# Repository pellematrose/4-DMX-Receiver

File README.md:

# DMX Receiver for the Raspberry Pi Pico

Firmware for a Raspberry Pi Pico (RP2040) that reads a DMX512 signal and drives four channels as RGBW — simultaneously as PWM on four power outputs and mirrored to a WS2812 pixel. It is operated with three buttons and a 128×64 OLED. Without a DMX signal, built-in auto effects run instead.
## Features
- DMX512 reception of the full 512-channel universe
- 4 output channels (R, G, B, W) from a freely selectable start address
- 800mA output current
- USB-C PD input 20V
- Configurable number of channels in use (1–4)
- RGBW output as PWM (500 Hz) and in parallel on a WS2812/NeoPixel
- OLED menu with buttons: start address, channel count, auto effect
- Settings are stored in EEPROM and restored on boot
- DMX takes priority: as soon as a signal is present, the auto effect is overridden
- Display turns off after 5 s of inactivity; the first button press wakes it
- At boot the firmware checks for DMX; without a signal the color fade starts automatically
## Auto effects

| Effect     | Description                                    |
| ---------- | ---------------------------------------------- |
| LED Auto   | Endless fade Red → Green → Blue                |
| Only White | White on all channels (W = 255 only)           |
| Blue-Green | Fade Blue ↔ Green with a 5 s pause at each end |
## Hardware / pinout

| Function    | GPIO | Note                                     |
| ----------- | ---- | ---------------------------------------- |
| DMX RX      | 0    | `dmxInput.begin(0, 1, 512)` – RX = GPIO0 |
| Button UP   | 3    | to GND, internal pull-up                 |
| Button MODE | 4    | to GND, internal pull-up                 |
| Button DOWN | 5    | to GND, internal pull-up                 |
| LED White   | 9    | PWM                                      |
| LED Blue    | 10   | PWM                                      |
| LED Green   | 11   | PWM                                      |
| LED Red     | 12   | PWM                                      |
| OLED SDA    | 14   | I2C (Wire1)                              |
| OLED SCL    | 15   | I2C (Wire1)                              |
| WS2812 data | 16   | 1 pixel                                  |
OLED: SSD1306, 128×64, I2C address `0x3C`.

The DMX input needs an RS-485 transceiver (e.g. MAX485) running at 3.3 V; twist the A/B pair and don't forget bus termination at both ends.
## Operation
**Main menu** (MODE to enter, UP/DOWN to scroll):
1. `DMX` → set start address and channel count
2. `AUTO` → choose an auto effect and start it with MODE

**In the DMX submenu:** MODE switches between *Start Addr* and *Num Channel*. UP/DOWN changes the value; MODE on the second field saves and returns. The address is automatically clamped so all channels fit inside the universe (max. `512 - channels + 1`).

**In the AUTO submenu:** UP/DOWN selects an effect, MODE starts it and returns to the main menu.
## Build
Platformio with the **Raspberry Pi Pico / RP2040** core (Earle Philhower).
Required libraries:
- `DmxInput` (DMX input via PIO, by )
- `Adafruit SSD1306`
- `Adafruit GFX Library`
- `Adafruit NeoPixel`
- `EEPROM` (included in the RP2040 core)
Board: *Raspberry Pi Pico*, sketch: `dmx_receiver.ino`.
## Notes
- When idle without DMX, the display does not refresh continuously — it redraws only on button presses and every 250 ms in the main menu.
- DMX handling is non-blocking, so buttons and display stay responsive even when the signal drops out.
- `buffer[0]` is the DMX start byte, which is why channel evaluation begins at `address + i` in the buffered universe.
# Not included in the Repo
- Some LEDs to light up
## License
GPL-3.0-or-later, for Firmware, see `LICENSE`. Copyright (c) 2026 Per-Simon Saal.

CERN-OHL-S-2.0, for Hardware and Enclosure, see `LICENSE`. Copyriht (c) 2026 Per-Simon Saal.

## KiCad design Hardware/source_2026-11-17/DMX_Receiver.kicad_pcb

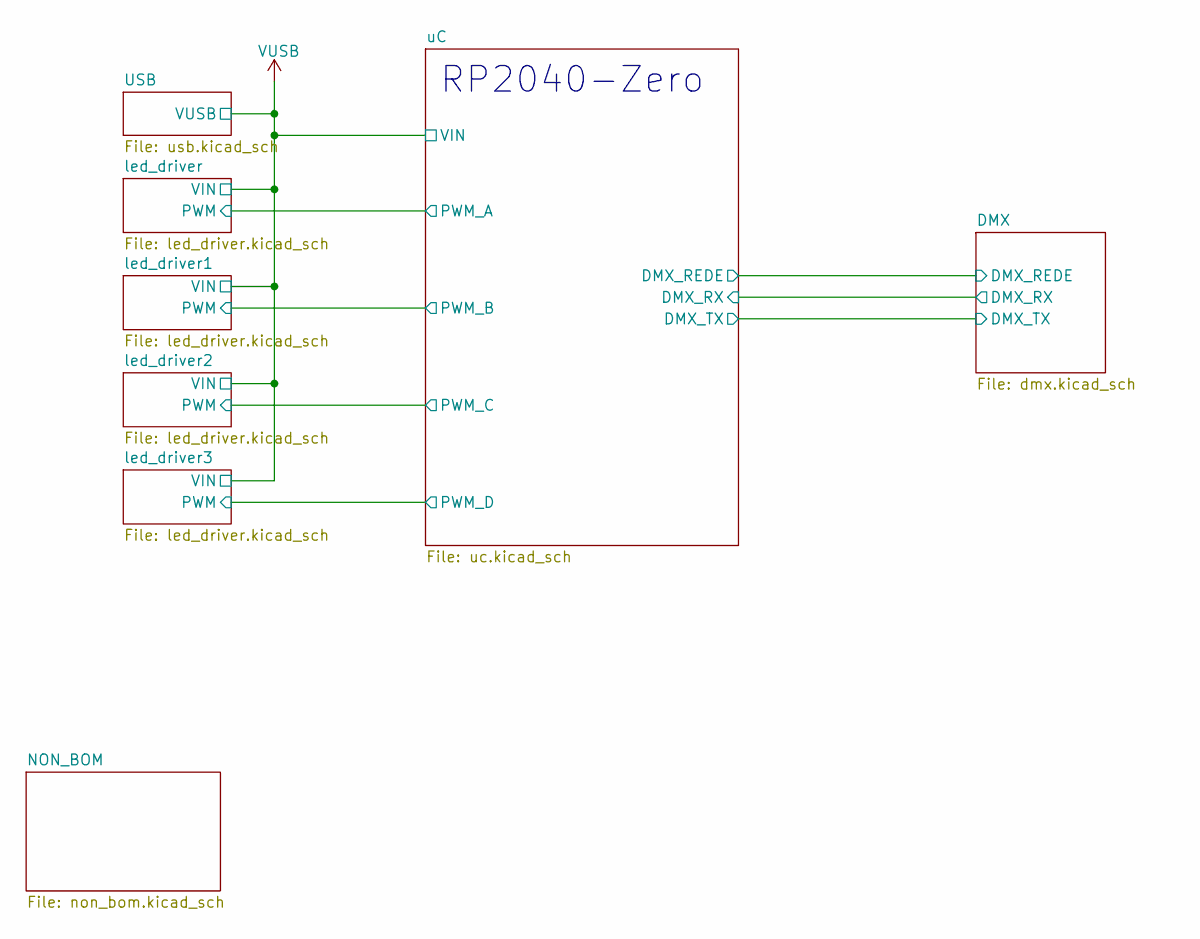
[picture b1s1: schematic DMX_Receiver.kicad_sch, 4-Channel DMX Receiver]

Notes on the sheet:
RP2040-Zero

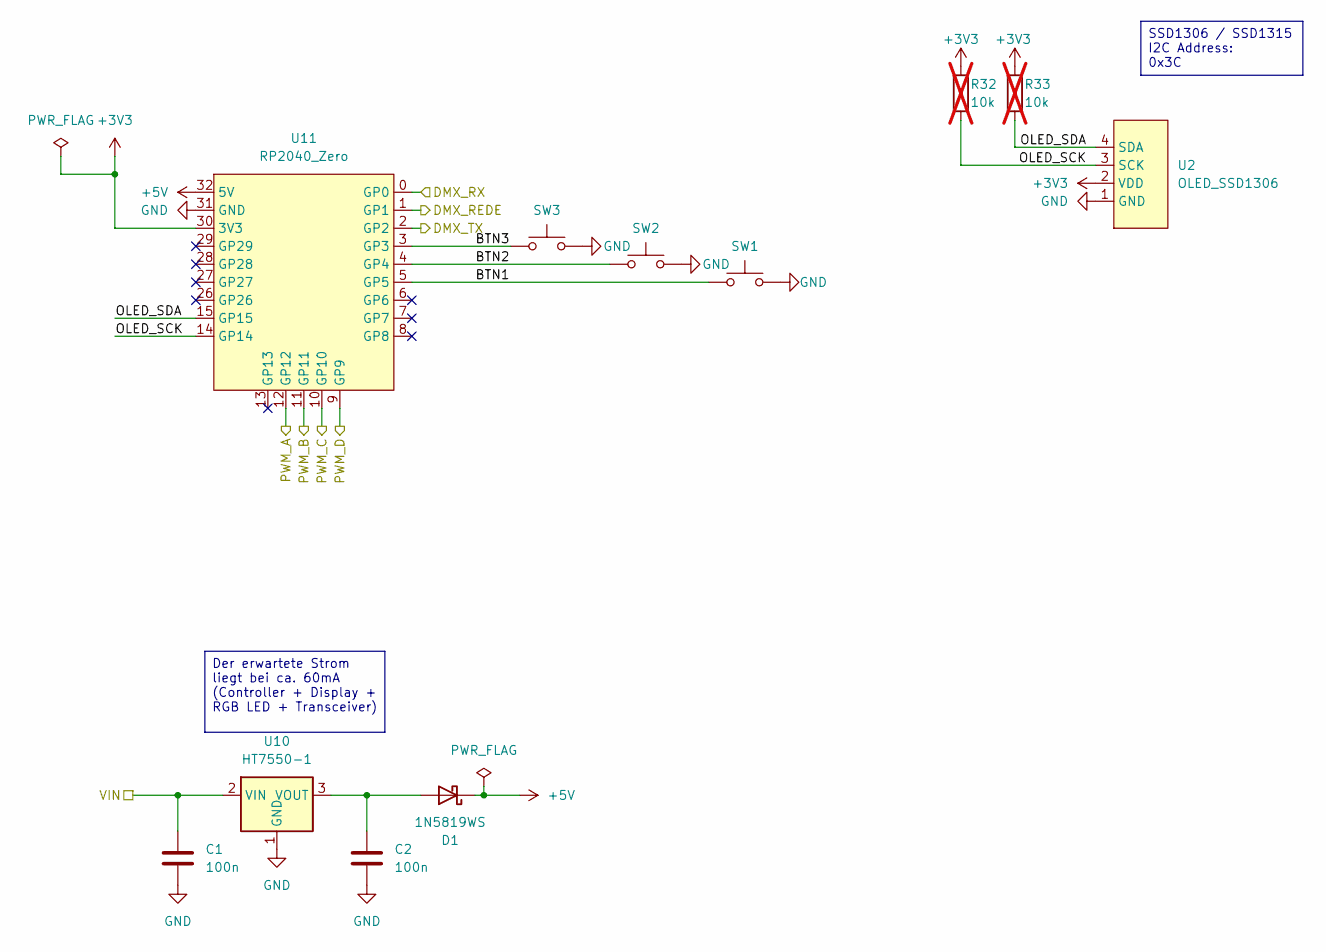
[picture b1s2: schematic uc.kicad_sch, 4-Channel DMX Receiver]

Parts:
C1, C2: 100n; C_0603_1608Metric; LCSC C14663
D1: 1N5819WS; D_SOD-323; LCSC C191023
R32, R33: 10k; R_0603_1608Metric; LCSC C25804; not fitted
SW1, SW2, SW3: SW_MEC_5G; Xunpu TS-1088
U2: OLED_SSD1306; SSD1306_0.96_Oled_wo_Holes
U10: HT7550-1; SOT-89-3; LCSC C16106
U11: RP2040_Zero; RP2040-Zero_SMD

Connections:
+3V3: R32.1, R33.1, U2.2 (VDD), U11.30 (3V3); also elsewhere on the board
+5V: D1.1 (K), U11.32 (5V)
/DMX/DMX_REDE: U11.1 (GP1); also elsewhere on the board
/DMX/DMX_RX: U11.0 (GP0); also elsewhere on the board
/DMX/DMX_TX: U11.2 (GP2); also elsewhere on the board
/led_driver1/PWM: U11.11 (GP11); also elsewhere on the board
/led_driver2/PWM: U11.10 (GP10); also elsewhere on the board
/led_driver3/PWM: U11.9 (GP9); also elsewhere on the board
/led_driver/PWM: U11.12 (GP12); also elsewhere on the board
/uC/BTN1: SW1.2 (B), U11.5 (GP5)
/uC/BTN2: SW2.2 (B), U11.4 (GP4)
/uC/BTN3: SW3.2 (B), U11.3 (GP3)
/uC/OLED_SCK: R32.2, U2.3 (SCK), U11.14 (GP14)
/uC/OLED_SDA: R33.2, U2.4 (SDA), U11.15 (GP15)
GND: C1.2, C2.2, SW1.1 (A), SW2.1 (A), SW3.1 (A), U2.1 (GND), U10.1 (GND), U11.31 (GND); also elsewhere on the board
unnamed: C2.1, D1.2 (A), U10.3 (VOUT)
VUSB: C1.1, U10.2 (VIN); also elsewhere on the board

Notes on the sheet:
Der erwartete Strom liegt bei ca. 60mA (Controller + Display + RGB LED + Transceiver)
SSD1306 / SSD1315 I2C Address: 0x3C

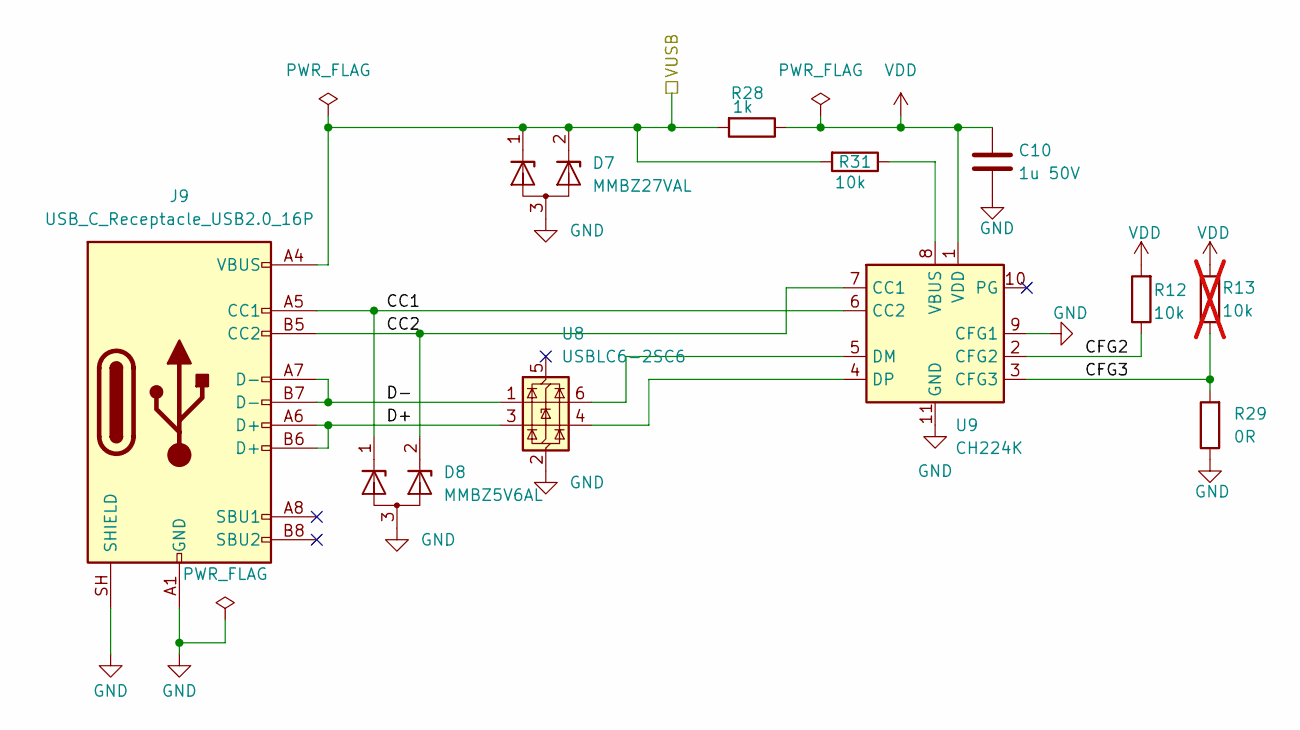
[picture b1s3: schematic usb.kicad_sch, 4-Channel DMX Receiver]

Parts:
C10: 1u 50V; C_0603_1608Metric; LCSC C15849
D7: MMBZ27VAL; SOT-23; LCSC C502597
D8: MMBZ5V6AL; SOT-23; LCSC C502591
J9: USB_C_Receptacle_USB2.0_16P; USB_C_Receptacle_GCT_USB4105-xx-A_16P_TopMnt_Horizontal; LCSC C2988369
R12, R31: 10k; R_0603_1608Metric; LCSC C25804
R13: 10k; R_0603_1608Metric; LCSC C25804; not fitted
R28: 1k; R_0603_1608Metric; LCSC C21190
R29: 0R; R_0603_1608Metric; LCSC C25804
U8: USBLC6-2SC6; SOT-23-6; LCSC C7519
U9: CH224K; SSOP-10-1EP_3.9x4.9mm_P1mm_EP2.1x3.3mm; LCSC C970725

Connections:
/USB/CC1: D8.1 (K), J9.A5 (CC1), U9.6 (CC2)
/USB/CC2: D8.2 (K), J9.B5 (CC2), U9.7 (CC1)
/USB/CFG2: R12.1, U9.2 (CFG2)
/USB/CFG3: R13.1, R29.2, U9.3 (CFG3)
/USB/D+: J9.A6 (D+), J9.B6 (D+), U8.3 (I/O2)
/USB/D-: J9.A7 (D-), J9.B7 (D-), U8.1 (I/O1)
GND: C10.1, D7.3 (A), D8.3 (A), J9.A1 (GND), J9.A12 (GND), J9.B1 (GND), J9.B12 (GND), J9.SH (SHIELD), R29.1, U8.2 (GND), U9.9 (CFG1), U9.11 (GND); also elsewhere on the board
unnamed: U8.6 (I/O1), U9.5 (DM)
unnamed: U8.4 (I/O2), U9.4 (DP)
unnamed: R31.1, U9.8 (VBUS)
VDD: C10.2, R12.2, R13.2, R28.1, U9.1 (VDD)
VUSB: D7.1 (K), D7.2 (K), J9.A4 (VBUS), J9.A9 (VBUS), J9.B4 (VBUS), J9.B9 (VBUS), R28.2, R31.2; also elsewhere on the board

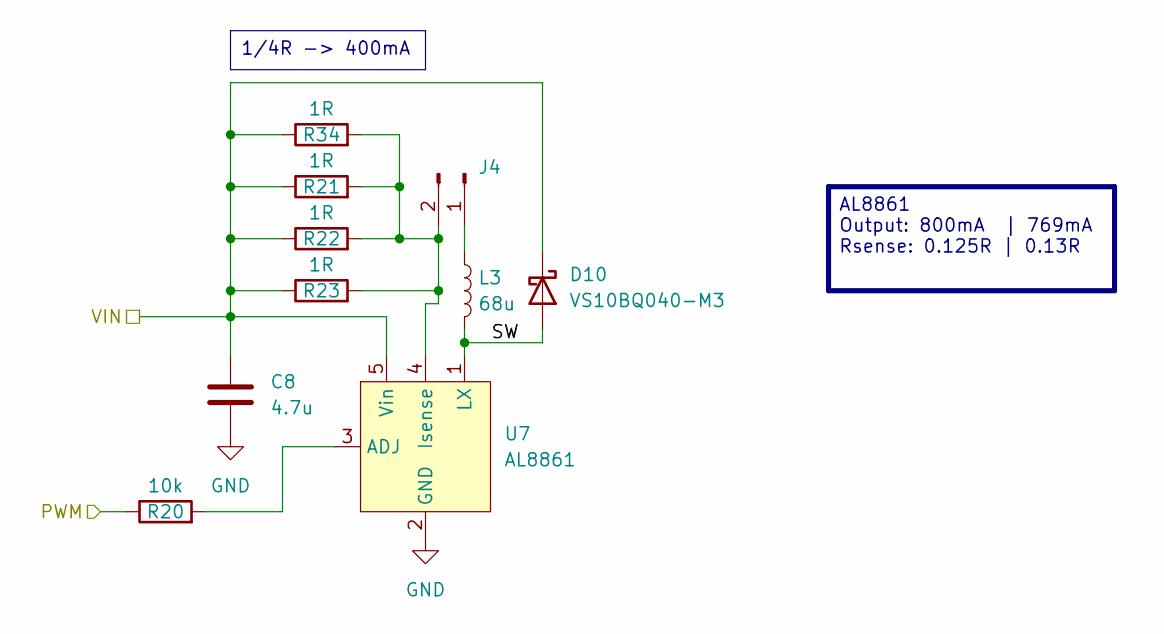
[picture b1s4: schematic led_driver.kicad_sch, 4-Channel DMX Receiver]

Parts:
C8: 4.7u; C_1206_3216Metric; LCSC C29823
D10: VS10BQ040-M3; D_SMB; LCSC C28646277
J4: Conn_01x02_Pin; PinHeader_1x02_P2.54mm_Vertical
L3: 68u; L_TDK_VLS6045EX_VLS6045AF; LCSC C404506
R20: 10k; R_0603_1608Metric; LCSC C25804
R21, R22, R23, R34: 1R; R_0603_1608Metric; LCSC C22936
U7: AL8861; SOT-23-5; LCSC C581338

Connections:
/led_driver/PWM: R20.1; also elsewhere on the board
/led_driver/SW: D10.2 (A), L3.2, U7.1 (LX)
GND: C8.2, U7.2 (GND); also elsewhere on the board
unnamed: J4.1, L3.1
unnamed: J4.2, R21.2, R22.2, R23.2, R34.2, U7.4 (Isense)
unnamed: R20.2, U7.3 (ADJ)
VUSB: C8.1, D10.1 (K), R21.1, R22.1, R23.1, R34.1, U7.5 (Vin); also elsewhere on the board

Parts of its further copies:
C3, C7, C9: 4.7u; C_1206_3216Metric; LCSC C29823
D3, D4, D5: VS10BQ040-M3; D_SMB; LCSC C28646277
J5, J7, J8: Conn_01x02_Pin; PinHeader_1x02_P2.54mm_Vertical
L1, L2, L4: 68u; L_TDK_VLS6045EX_VLS6045AF; LCSC C404506
R2, R3, R4, R5, R15, R16, R17, R18, R24, R25, R26, R27: 1R; R_0603_1608Metric; LCSC C22936
R14, R19, R35: 10k; R_0603_1608Metric; LCSC C25804
U4, U5, U6: AL8861; SOT-23-5; LCSC C581338

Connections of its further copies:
/led_driver1/PWM: R14.1; also elsewhere on the board
/led_driver1/SW: D3.2 (A), L1.2, U4.1 (LX)
/led_driver2/PWM: R19.1; also elsewhere on the board
/led_driver2/SW: D4.2 (A), L2.2, U5.1 (LX)
/led_driver3/PWM: R35.1; also elsewhere on the board
/led_driver3/SW: D5.2 (A), L4.2, U6.1 (LX)
GND: C3.2, C7.2, C9.2, U4.2 (GND), U5.2 (GND), U6.2 (GND); also elsewhere on the board
unnamed: J5.1, L1.1
unnamed: J5.2, R2.2, R3.2, R4.2, R5.2, U4.4 (Isense)
unnamed: J7.1, L2.1
unnamed: J7.2, R15.2, R16.2, R17.2, R18.2, U5.4 (Isense)
unnamed: J8.1, L4.1
unnamed: J8.2, R24.2, R25.2, R26.2, R27.2, U6.4 (Isense)
unnamed: R14.2, U4.3 (ADJ)
unnamed: R19.2, U5.3 (ADJ)
unnamed: R35.2, U6.3 (ADJ)
VUSB: C3.1, C7.1, C9.1, D3.1 (K), D4.1 (K), D5.1 (K), R2.1, R3.1, R4.1, R5.1, R15.1, R16.1, R17.1, R18.1, R24.1, R25.1, R26.1, R27.1, U4.5 (Vin), U5.5 (Vin), U6.5 (Vin); also elsewhere on the board

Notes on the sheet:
AL8861 Output: 800mA | 769mA Rsense: 0.125R | 0.13R
1/4R -> 400mA

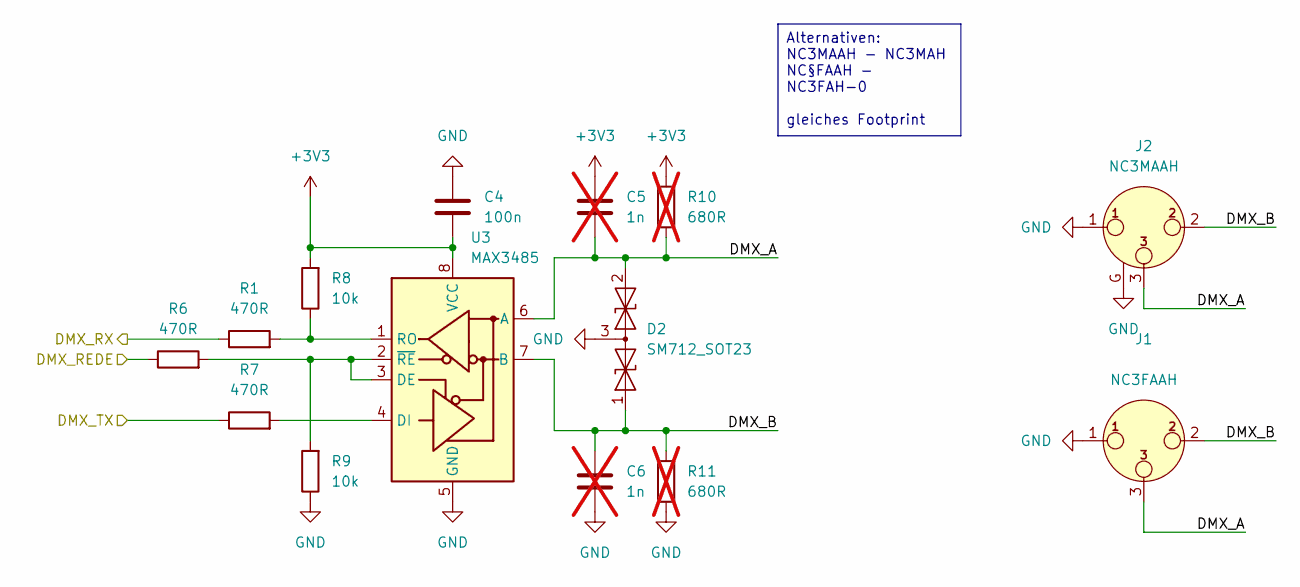
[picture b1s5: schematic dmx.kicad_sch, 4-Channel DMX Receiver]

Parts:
C4: 100n; C_0603_1608Metric; LCSC C14663
C5, C6: 1n; C_0603_1608Metric; not fitted
D2: SM712_SOT23; SOT-23; LCSC C521963
J1: NC3FAAH; Jack_XLR_Neutrik_NC3FAAH_Horizontal; LCSC C368463
J2: NC3MAAH; Jack_XLR_Neutrik_NC3MAAH_Horizontal; LCSC C368521
R1, R6, R7: 470R; R_0603_1608Metric; LCSC C23179
R8, R9: 10k; R_0603_1608Metric; LCSC C25804
R10, R11: 680R; R_0603_1608Metric; not fitted
U3: MAX3485; SOIC-8_3.9x4.9mm_P1.27mm; LCSC C8963

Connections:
+3V3: C4.2, C5.1, R8.2, R10.2, U3.8 (VCC); also elsewhere on the board
/DMX/DMX_A: C5.2, D2.2 (A2), J1.3, J2.3, R10.1, U3.6 (A)
/DMX/DMX_B: C6.1, D2.1 (A1), J1.2, J2.2, R11.2, U3.7 (B)
/DMX/DMX_REDE: R6.1; also elsewhere on the board
/DMX/DMX_RX: R1.1; also elsewhere on the board
/DMX/DMX_TX: R7.1; also elsewhere on the board
GND: C4.1, C6.2, D2.3 (common), J1.1, J2.1, J2.G, R9.1, R11.1, U3.5 (GND); also elsewhere on the board
unnamed: R6.2, R9.2, U3.2 (~RE), U3.3 (DE)
unnamed: R7.2, U3.4 (DI)
unnamed: R1.2, R8.1, U3.1 (RO)

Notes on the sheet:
Alternativen: NC3MAAH - NC3MAH NC§FAAH - NC3FAH-0 gleiches Footprint

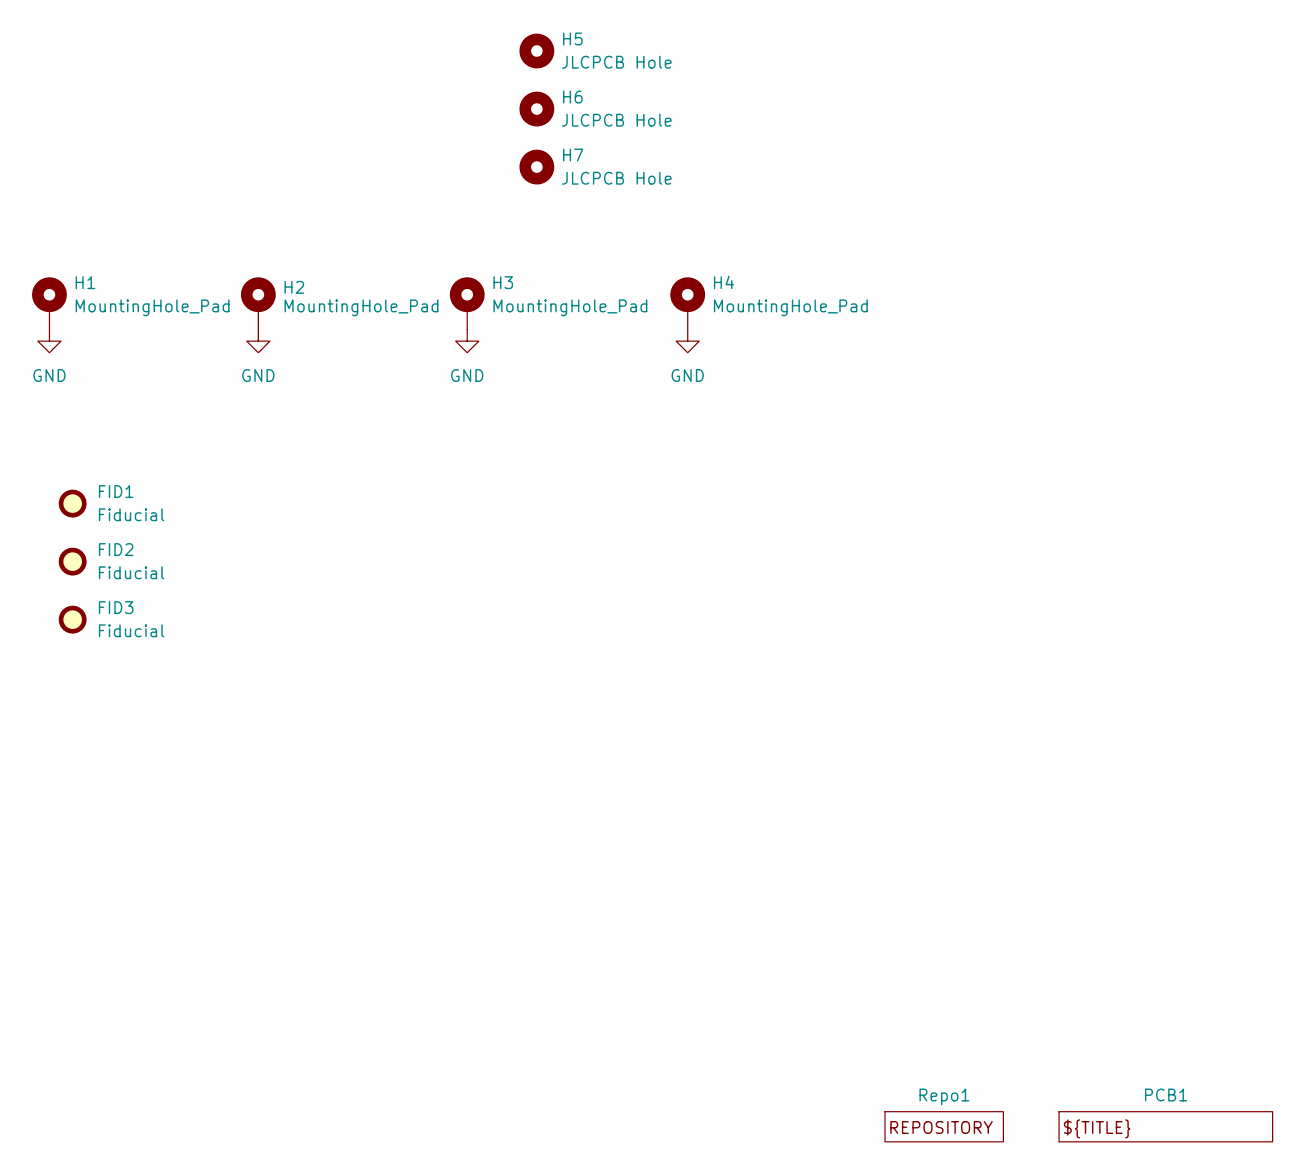
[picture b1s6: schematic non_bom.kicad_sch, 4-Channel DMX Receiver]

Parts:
FID1, FID2, FID3: Fiducial; Fiducial_1.5mm_Mask3mm
H1, H2, H3, H4: MountingHole_Pad; MountingHole_3.2mm_M3_DIN965_Pad_TopBottom
H5, H6, H7: JLCPCB Hole; Mounting_Hole_JLC
PCB1: _PCB
Repo1: _Repository

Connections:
GND: H1.1 (1_1), H2.1 (1_1), H3.1 (1_1), H4.1 (1_1); also elsewhere on the board

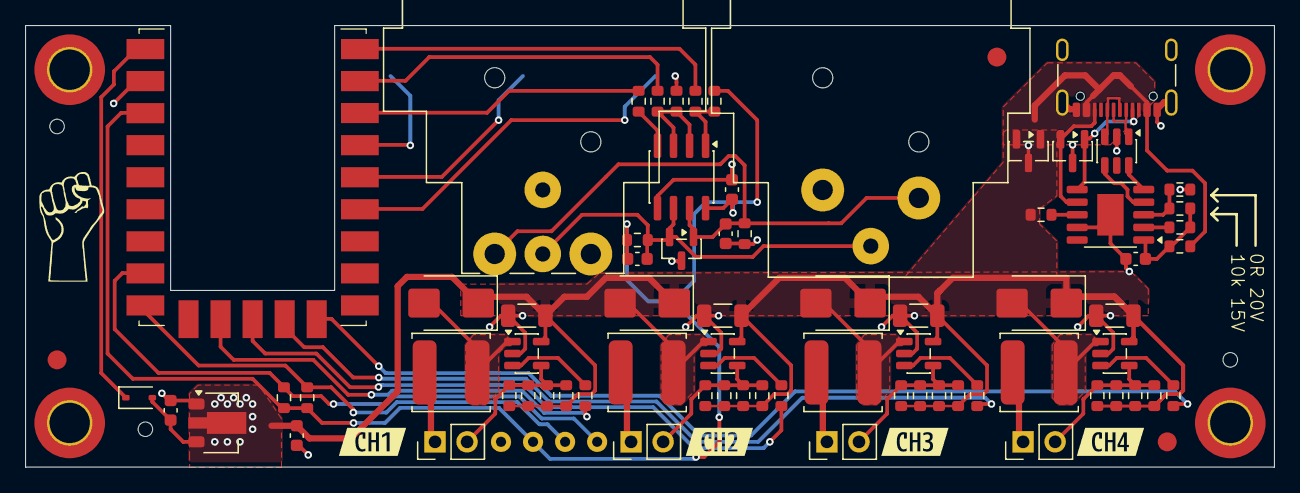
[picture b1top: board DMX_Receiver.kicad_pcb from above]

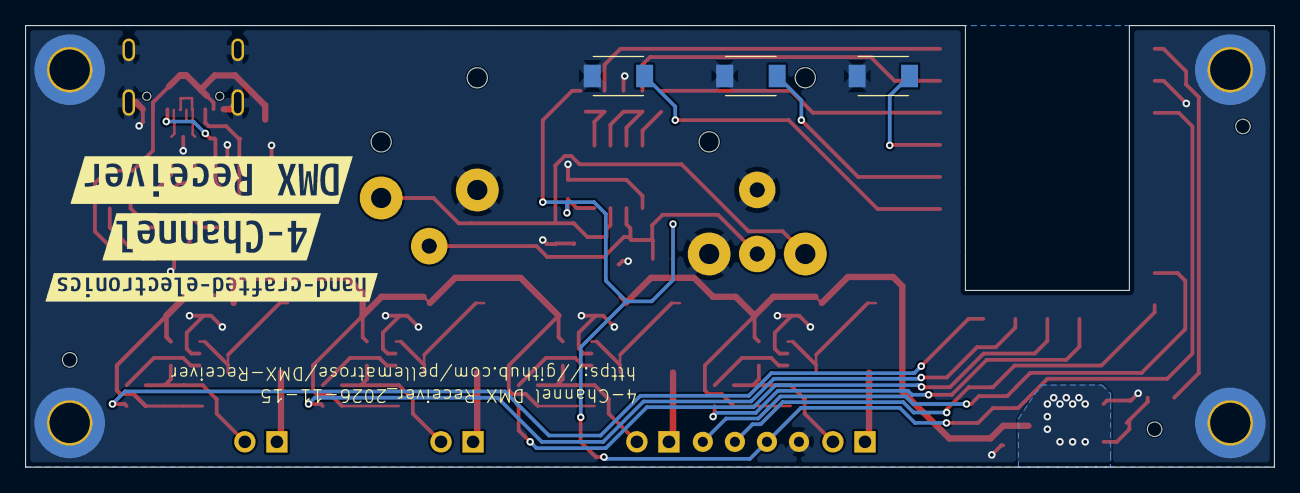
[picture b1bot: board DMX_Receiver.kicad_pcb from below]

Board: 2 copper layers, 99.0 x 35.0 mm, 95 parts (9 on the bottom side), 48 nets.

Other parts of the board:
kibuzzard-687C165A: G***; kibuzzard-687C165A
kibuzzard-687C1666: G***; kibuzzard-687C1666
kibuzzard-68753E61: G***; kibuzzard-68753E61
kibuzzard-68753E70: G***; kibuzzard-68753E70
kibuzzard-68753E79: G***; kibuzzard-68753E79
kibuzzard-68753E88: G***; kibuzzard-68753E88
kibuzzard-687537A4: G***; kibuzzard-687537A4

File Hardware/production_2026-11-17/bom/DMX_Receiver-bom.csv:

"Reference","QUANTITY","Value","Footprint","LCSC","Digikey","Mouser"
"C1,C2,C4","3","100n","Capacitor_SMD:C_0603_1608Metric","C14663","",""
"C3,C7-C9","4","4.7u","Capacitor_SMD:C_1206_3216Metric","C29823","",""
"C10","1","1u 50V","Capacitor_SMD:C_0603_1608Metric","C15849","",""
"D1","1","1N5819WS","Diode_SMD:D_SOD-323","C191023","",""
"D2","1","SM712_SOT23","Package_TO_SOT_SMD:SOT-23","C521963","",""
"D3-D5,D10","4","VS10BQ040-M3","Diode_SMD:D_SMB","C28646277","",""
"D7","1","MMBZ27VAL","Package_TO_SOT_SMD:SOT-23","C502597","",""
"D8","1","MMBZ5V6AL","Package_TO_SOT_SMD:SOT-23","C502591","",""
"J1","1","NC3FAAH","Connector_Audio:Jack_XLR_Neutrik_NC3FAAH_Horizontal","C368463","",""
"J2","1","NC3MAAH","Connector_Audio:Jack_XLR_Neutrik_NC3MAAH_Horizontal","C368521","",""
"J4,J5,J7,J8","4","Conn_01x02_Pin","Connector_PinHeader_2.54mm:PinHeader_1x02_P2.54mm_Vertical","","",""
"J9","1","USB_C_Receptacle_USB2.0_16P","Connector_USB:USB_C_Receptacle_GCT_USB4105-xx-A_16P_TopMnt_Horizontal","C2988369","",""
"L1-L4","4","68u","Inductor_SMD:L_TDK_VLS6045EX_VLS6045AF","C404506","",""
"R1,R6,R7","3","470R","Resistor_SMD:R_0603_1608Metric","C23179","",""
"R2-R5,R15-R18,R21-R27,R34","16","1R","Resistor_SMD:R_0603_1608Metric","C22936","",""
"R8,R9,R12,R14,R19,R20,R31-R33,R35","10","10k","Resistor_SMD:R_0603_1608Metric","C25804","",""
"R28","1","1k","Resistor_SMD:R_0603_1608Metric","C21190","",""
"R29","1","0R","Resistor_SMD:R_0603_1608Metric","C25804","",""
"SW1-SW3","3","SW_MEC_5G","_PS_LIB_PCB:Xunpu TS-1088","","",""
"U2","1","OLED_SSD1306","_PS_LIB_PCB:SSD1306_0.96_Oled_wo_Holes","","",""
"U3","1","MAX3485","Package_SO:SOIC-8_3.9x4.9mm_P1.27mm","C8963","",""
"U4-U7","4","AL8861","Package_TO_SOT_SMD:SOT-23-5","C581338","",""
"U8","1","USBLC6-2SC6","Package_TO_SOT_SMD:SOT-23-6","C7519","",""
"U9","1","CH224K","Package_SO:SSOP-10-1EP_3.9x4.9mm_P1mm_EP2.1x3.3mm","C970725","",""
"U10","1","HT7550-1","Package_TO_SOT_SMD:SOT-89-3","C16106","",""
"U11","1","RP2040_Zero","_PS_LIB_PCB:RP2040-Zero_SMD","","",""

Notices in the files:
Hardware/source_2026-11-17/DMX_Receiver.kicad_pcb:
CERN-OHL-S v2
© 2026 Per-Simon Saal
